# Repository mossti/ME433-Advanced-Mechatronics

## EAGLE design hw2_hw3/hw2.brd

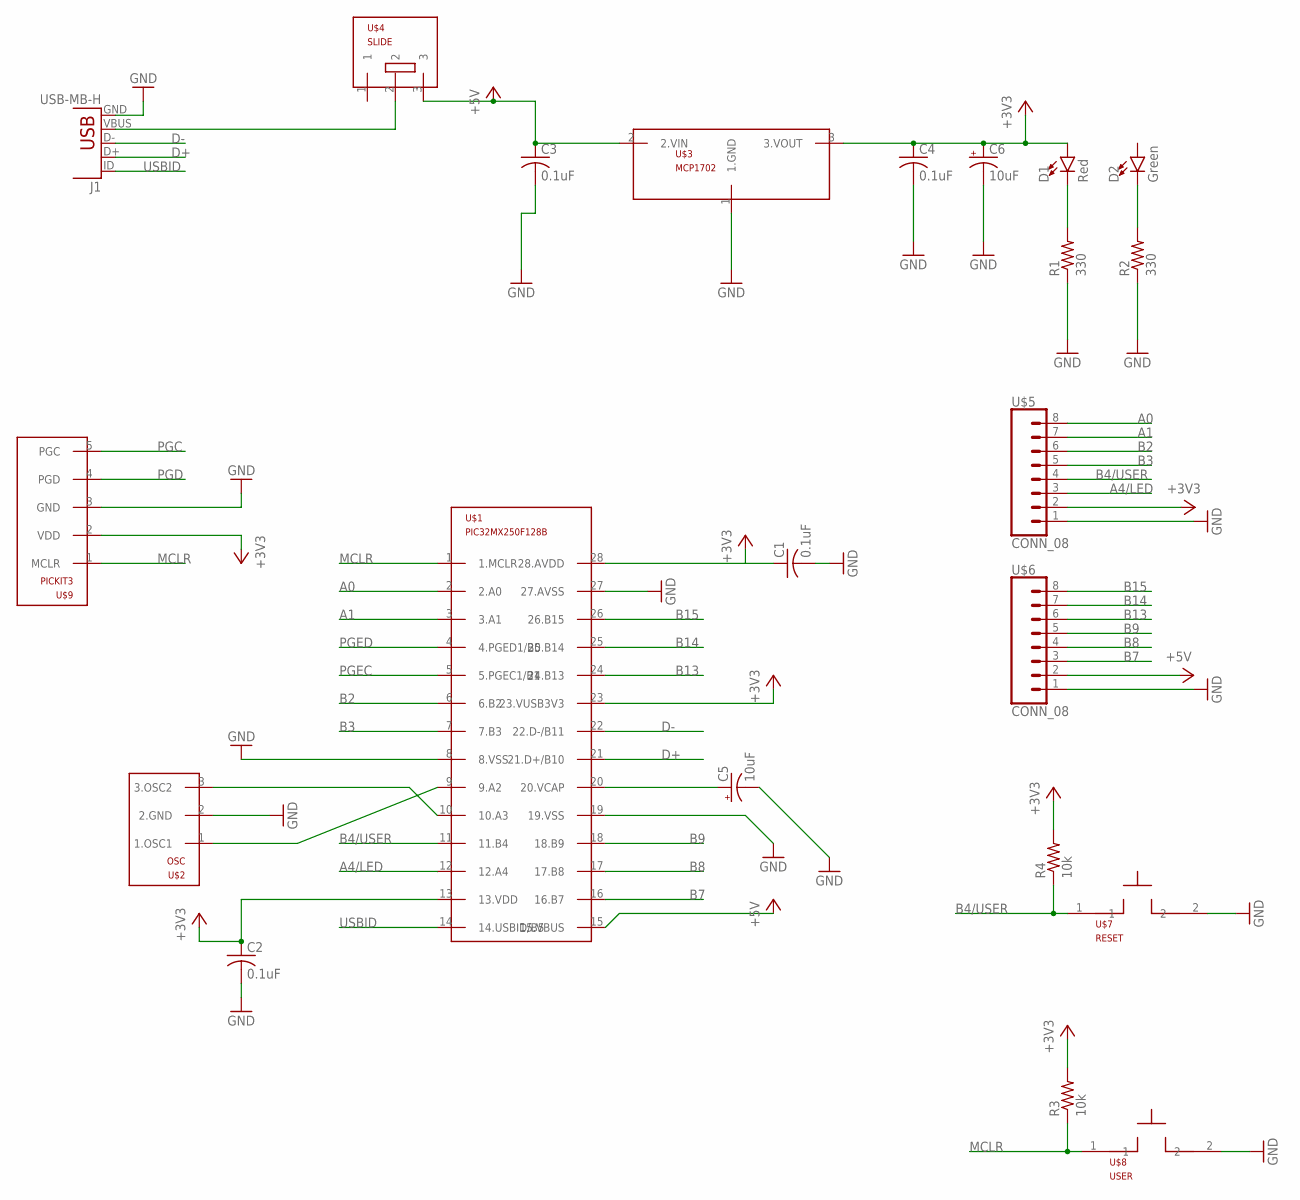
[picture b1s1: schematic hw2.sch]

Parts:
C1, C2, C3, C4: 0.1uF; C025-025X050
C5, C6: 10uF; B45181B
D1: Red; LED_3MM
D2: Green; LED_3MM
J1: USB-MB-H
R1, R2: 330; 0207/10
R3, R4: 10k; 0207/10
U$1: PIC32MX250F128B; DIL28-3
U$2: OSC
U$3: MCP1702; TO92
U$4: SLIDE
U$5, U$6: CONN_08; 1X08
U$7: RESET; PB
U$8: USER; PB
U$9: PICKIT3; 1X05

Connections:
+3V3: C2.1, C4.1, C6.+, D1.A, R3.2, R4.2, U$1.13 (13.VDD), U$1.23 (23.VUSB3V3), U$3.3 (3.VOUT), U$5.2, U$9.2 (VDD)
+5V: C3.1, U$1.15 (15.VBUS), U$3.2 (2.VIN), U$4.3, U$6.2
A0: U$1.2 (2.A0), U$5.8
A1: U$1.3 (3.A1), U$5.7
A4/LED: U$1.12 (12.A4), U$5.3
B2: U$1.6 (6.B2), U$5.6
B3: U$1.7 (7.B3), U$5.5
B4/USER: R4.1, U$1.11 (11.B4), U$5.4, U$7.1
B7: U$1.16 (16.B7), U$6.3
B8: U$1.17 (17.B8), U$6.4
B9: U$1.18 (18.B9), U$6.5
B13: U$1.24 (24.B13), U$6.6
B14: U$1.25 (25.B14), U$6.7
B15: U$1.26 (26.B15), U$6.8
D+: J1.D+, U$1.21 (21.D+/B10)
D-: J1.D-, U$1.22 (22.D-/B11)
GND: C1.2, C2.2, C3.2, C4.2, C5.-, C6.-, J1.GND, R1.1, R2.1, U$1.8 (8.VSS), U$1.19 (19.VSS), U$1.27 (27.AVSS), U$2.2 (2.GND), U$3.1 (1.GND), U$5.1, U$6.1, U$7.2, U$8.2, U$9.3 (GND)
MCLR: R3.1, U$1.1 (1.MCLR), U$8.1, U$9.1 (MCLR)
unnamed: J1.VBUS, U$4.2
unnamed: D1.K (C), R1.2
unnamed: D2.K (C), R2.2
unnamed: U$1.9 (9.A2), U$2.1 (1.OSC1)
unnamed: U$1.10 (10.A3), U$2.3 (3.OSC2)
unnamed: C5.+, U$1.20 (20.VCAP)
unnamed: C1.1, U$1.28 (28.AVDD)
PGC: U$9.5 (PGC)
PGD: U$9.4 (PGD)
PGEC: U$1.5 (5.PGEC1/B1)
PGED: U$1.4 (4.PGED1/B0)
USBID: J1.ID, U$1.14 (14.USBID/B5)

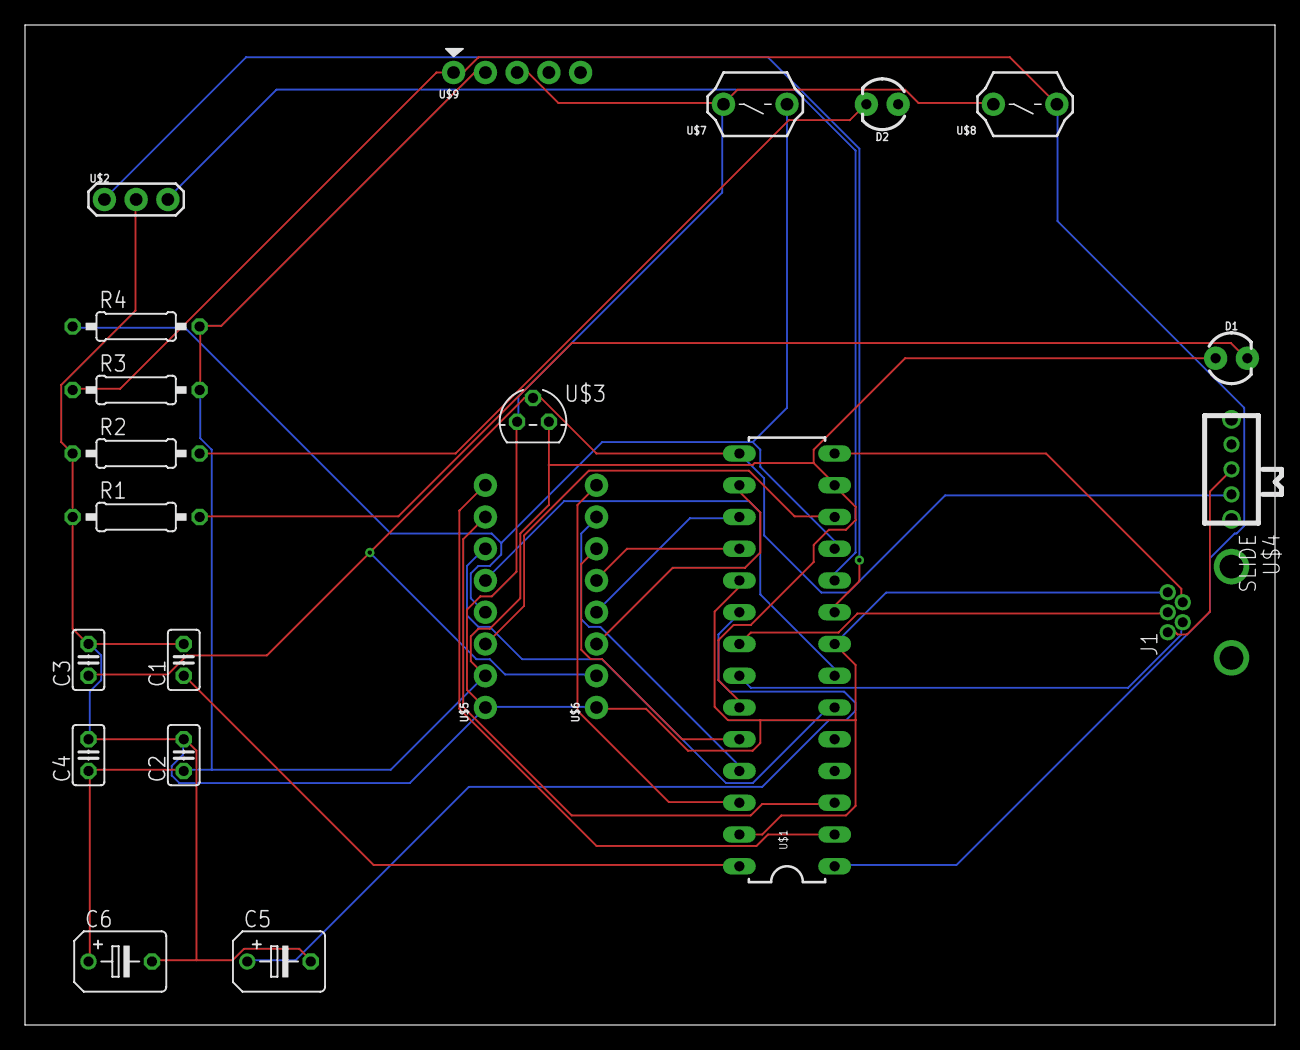
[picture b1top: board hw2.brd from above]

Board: 2 copper layers, 100.0 x 80.0 mm, 22 parts (0 on the bottom side), 26 nets.

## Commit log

2019-06-13 new repo upload; errors with old repo
2019-06-13 added hw5 schematic to new repo
2019-06-14 hw16 content

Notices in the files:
parts and their libraries:
SparkFun-LED: Licensing: Creative Commons ShareAlike 4.0 International - https://creativecommons.org/licenses/by-sa/4.0
